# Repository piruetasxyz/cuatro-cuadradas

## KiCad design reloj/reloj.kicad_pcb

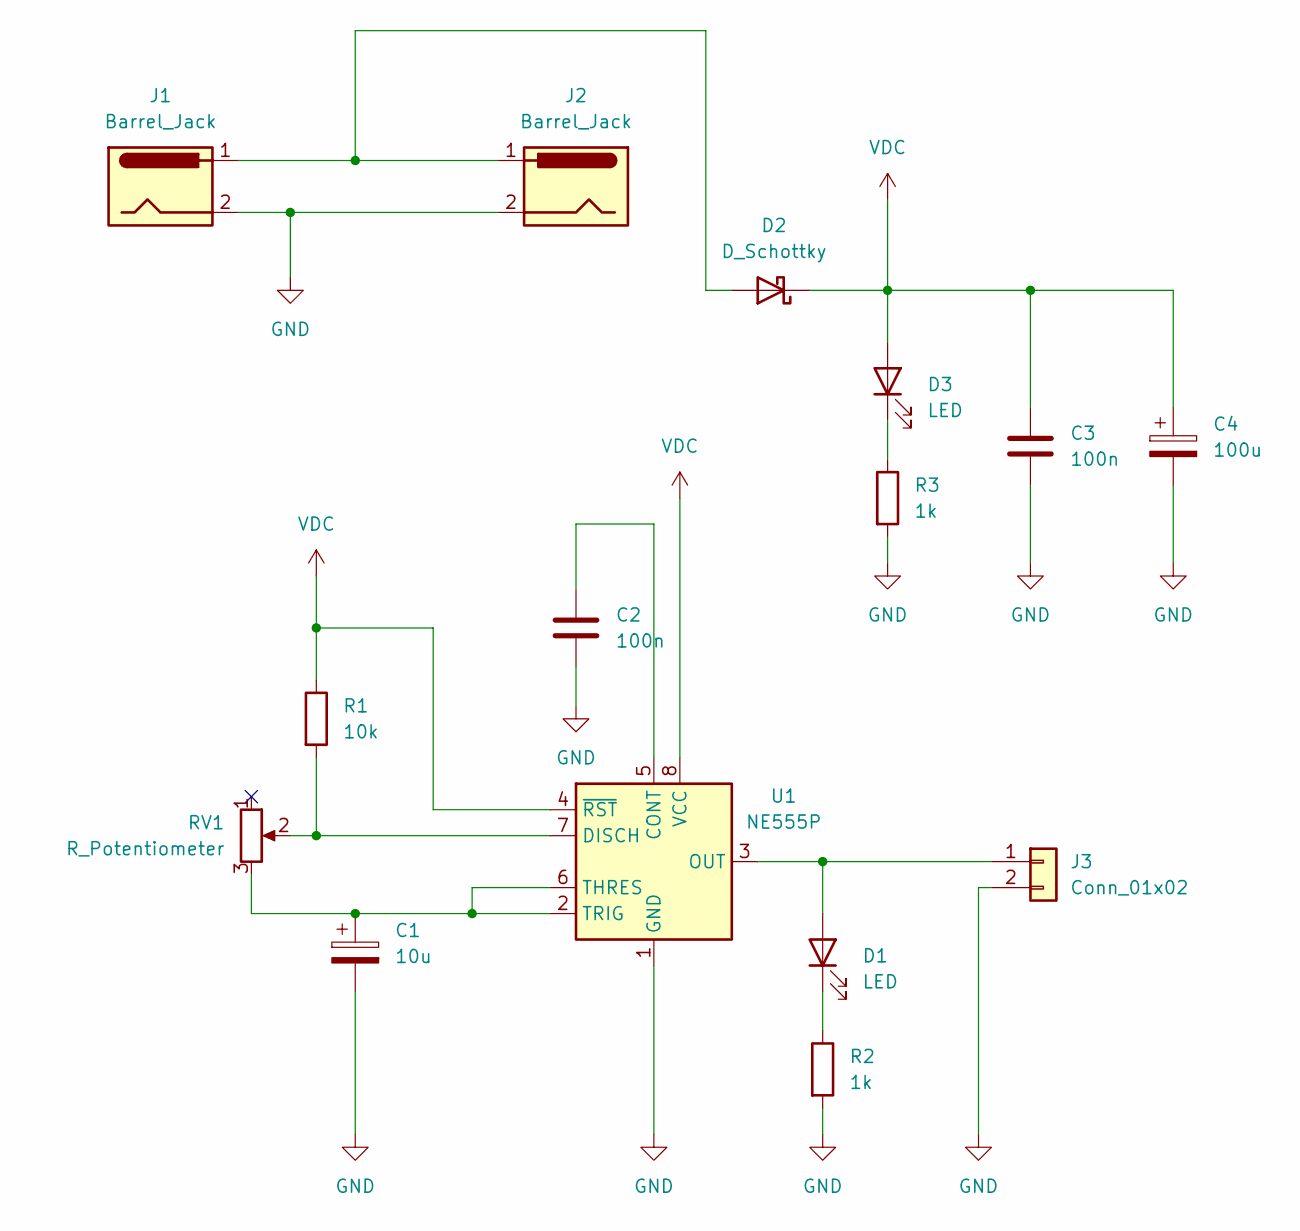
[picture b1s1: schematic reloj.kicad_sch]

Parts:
C1: 10u; CP_Elec_4x5.4; LCSC C3343
C2, C3: 100n; C_0402_1005Metric_Pad0.74x0.62mm_HandSolder
C4: 100u; CP_Elec_5x5.4
D1, D3: LED; LED_D5.0mm
D2: D_Schottky; D_SOD-123; LCSC C82544
J1, J2: Barrel_Jack; TerminalBlock_MaiXu_MX126-5.0-02P_1x02_P5.00mm
J3: Conn_01x02; Altech_AK100_1x02_P5.00mm
R1: 10k; R_0805_2012Metric_Pad1.20x1.40mm_HandSolder
R2, R3: 1k; R_0805_2012Metric_Pad1.20x1.40mm_HandSolder
RV1: R_Potentiometer; TerminalBlock_MaiXu_MX126-5.0-03P_1x03_P5.00mm
U1: NE555P; DIP-8_W7.62mm_Socket_LongPads

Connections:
GND: C1.2, C2.2, C3.2, C4.2, J1.2, J2.2, J3.2, R2.2, R3.2, U1.1 (GND)
unnamed: D1.2 (A), J3.1, U1.3 (OUT)
unnamed: D1.1 (K), R2.1
unnamed: D2.2 (A), J1.1, J2.1
unnamed: D3.1 (K), R3.1
unnamed: C2.1, U1.5 (CONT)
unnamed: R1.2, RV1.2, U1.7 (DISCH)
unnamed: C1.1, RV1.3, U1.2 (TRIG), U1.6 (THRES)
VDC: C3.1, C4.1, D2.1 (K), D3.2 (A), R1.1, U1.4 (~RST), U1.8 (VCC)

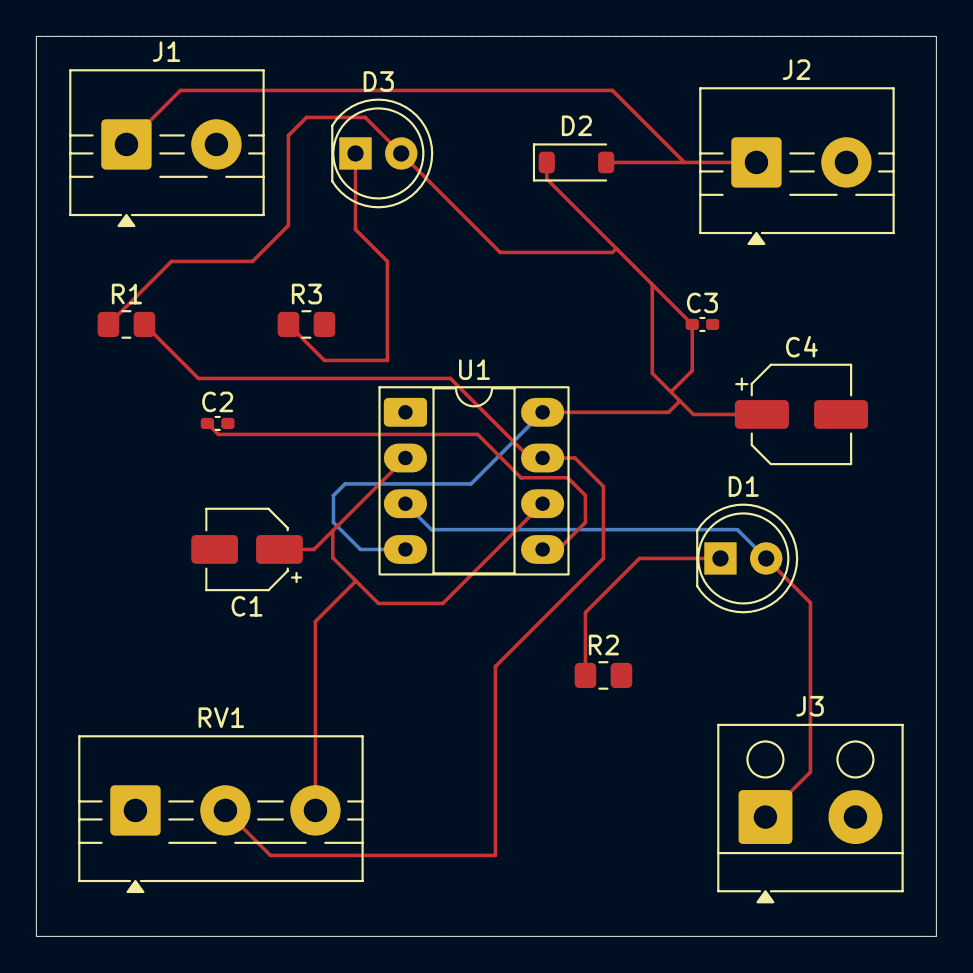
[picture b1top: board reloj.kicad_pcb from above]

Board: 2 copper layers, 50.0 x 50.0 mm, 15 parts (0 on the bottom side), 9 nets.

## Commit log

2026-04-22 agregar .gitignore
2026-04-22 agregar reloj y secuenciador
2026-04-22 agregar mezclador y osciladores
2026-05-02 agregar borradores
2026-05-13 agregar kicanvas.js
2026-05-13 agregar index.html de prueba
2026-05-13 agregar mas subtitulos
2026-05-13 convertir de a4 a a5
